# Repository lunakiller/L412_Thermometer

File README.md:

# L412 Thermometer
Temperature and humidity station powered by STM32L412KB MCU. The goal of the project is the longest possible battery life.

## Main components
- STM32L412KBT6 MCU
- Si7021 temperature and humidity sensor
- LCD display with PCD8544 driver
- 600mAh Li-Ion battery

## Goals
- [x] Build it on the breadboard
- [x] Show temperature and humidity data on the display
- [x] Run from the battery
- [x] Design PCB
- [ ] Measure battery voltage
- [ ] Sync time through USB
- [ ] Design 3D printed case

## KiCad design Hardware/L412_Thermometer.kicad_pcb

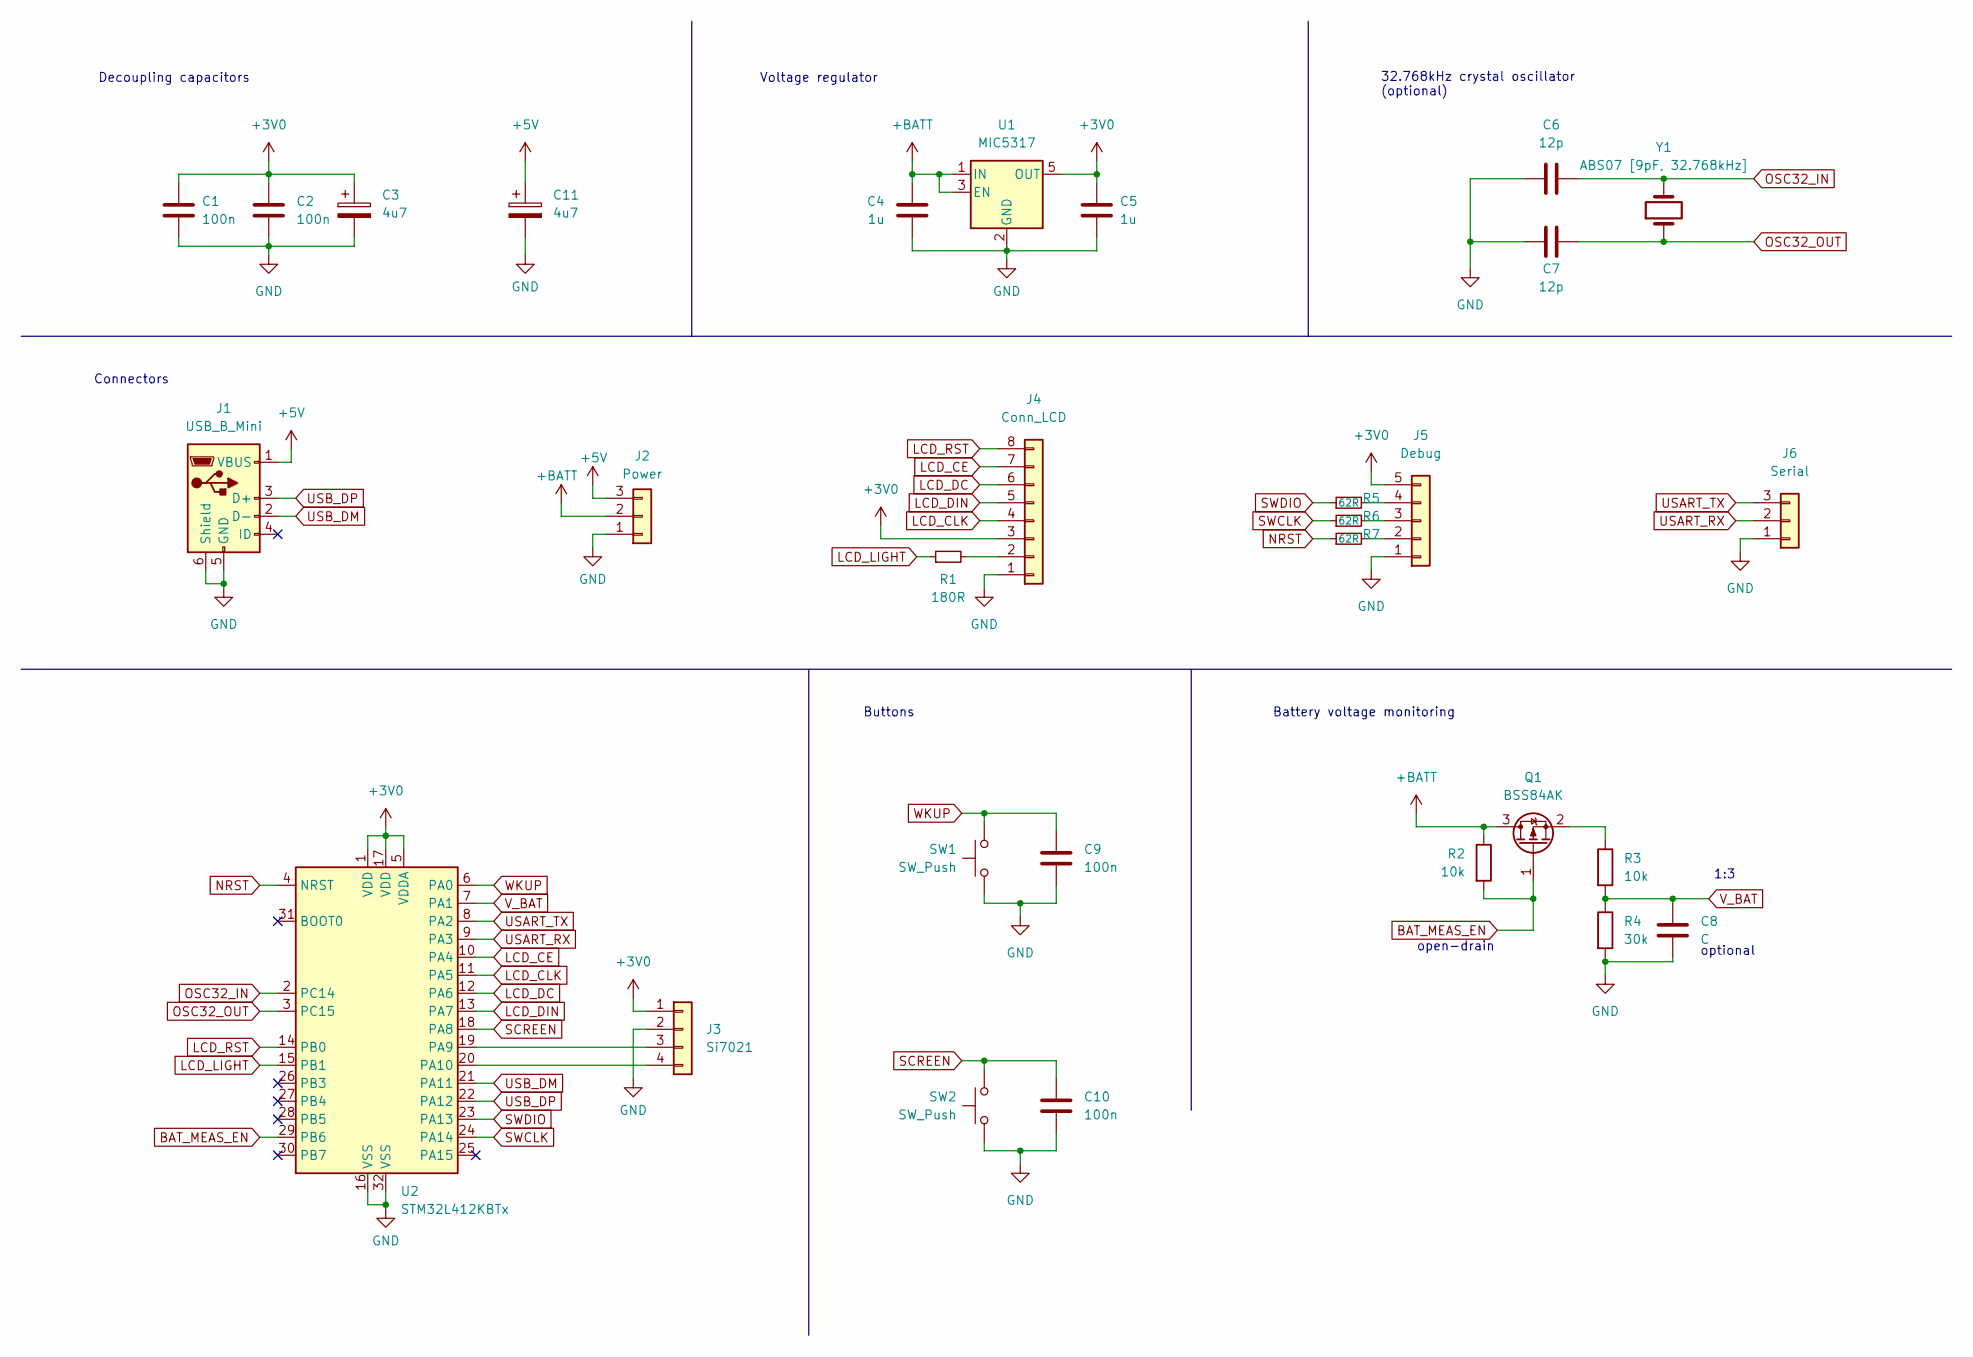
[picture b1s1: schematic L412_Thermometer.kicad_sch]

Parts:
C1, C2, C9, C10: 100n; C_0603_1608Metric
C3, C11: 4u7; CP_EIA-1608-10_AVX-L
C4, C5: 1u; C_0603_1608Metric
C6, C7: 12p; C_0603_1608Metric
C8: C; C_0603_1608Metric
J1: USB_B_Mini; USB_Mini-B_Lumberg_2486_01_Horizontal
J2: Power; PinHeader_1x03_P2.54mm_Vertical
J3: Si7021; PinHeader_1x04_P2.54mm_Vertical
J4: Conn_LCD; PinHeader_1x08_P2.54mm_Vertical
J5: Debug; PinHeader_1x05_P2.54mm_Vertical
J6: Serial; PinHeader_1x03_P2.54mm_Vertical
Q1: BSS84AK; SOT-23
R1: 180R; R_0603_1608Metric
R2, R3: 10k; R_0603_1608Metric
R4: 30k; R_0603_1608Metric
R5, R6, R7: 62R; R_0603_1608Metric
SW1, SW2: SW_Push; SW_SPST_SKQG_WithStem
U1: MIC5317; SOT-23-5
U2: STM32L412KBTx; LQFP-32_7x7mm_P0.8mm
Y1: ABS07 [9pF, 32.768kHz]; Crystal_SMD_3215-2Pin_3.2x1.5mm

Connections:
+3V0: C1.1, C2.1, C3.1, C5.1, J3.1, J4.3, J5.5, U1.5 (OUT), U2.1 (VDD), U2.5 (VDDA), U2.17 (VDD)
+5V: C11.1, J1.1 (VBUS), J2.3
+BATT: C4.1, J2.2, Q1.3 (D), R2.1, U1.1 (IN), U1.3 (EN)
BAT_MEAS_EN: Q1.1 (G), R2.2, U2.29 (PB6)
GND: C1.2, C2.2, C3.2, C4.2, C5.2, C6.1, C7.1, C8.2, C9.2, C10.2, C11.2, J1.5 (GND), J1.6 (Shield), J2.1, J3.2, J4.1, J5.1, J6.1, R4.2, SW1.1, SW2.1, U1.2 (GND), U2.16 (VSS), U2.32 (VSS)
LCD_CE: J4.7, U2.10 (PA4)
LCD_CLK: J4.4, U2.11 (PA5)
LCD_DC: J4.6, U2.12 (PA6)
LCD_DIN: J4.5, U2.13 (PA7)
LCD_LIGHT: R1.1, U2.15 (PB1)
LCD_RST: J4.8, U2.14 (PB0)
NRST: R7.1, U2.4 (NRST)
unnamed: J3.3, U2.19 (PA9)
unnamed: J3.4, U2.20 (PA10)
unnamed: J4.2, R1.2
unnamed: J5.2, R7.2
unnamed: J5.3, R6.2
unnamed: J5.4, R5.2
unnamed: Q1.2 (S), R3.1
OSC32_IN: C6.2, U2.2 (PC14), Y1.2
OSC32_OUT: C7.2, U2.3 (PC15), Y1.1
SCREEN: C10.1, SW2.2, U2.18 (PA8)
SWCLK: R6.1, U2.24 (PA14)
SWDIO: R5.1, U2.23 (PA13)
USART_RX: J6.2, U2.9 (PA3)
USART_TX: J6.3, U2.8 (PA2)
USB_DM: J1.2 (D-), U2.21 (PA11)
USB_DP: J1.3 (D+), U2.22 (PA12)
V_BAT: C8.1, R3.2, R4.1, U2.7 (PA1)
WKUP: C9.1, SW1.2, U2.6 (PA0)

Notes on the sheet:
1:3
Battery voltage monitoring
Buttons
open-drain
optional
32.768kHz crystal oscillator (optional)
Voltage regulator
Decoupling capacitors
Connectors

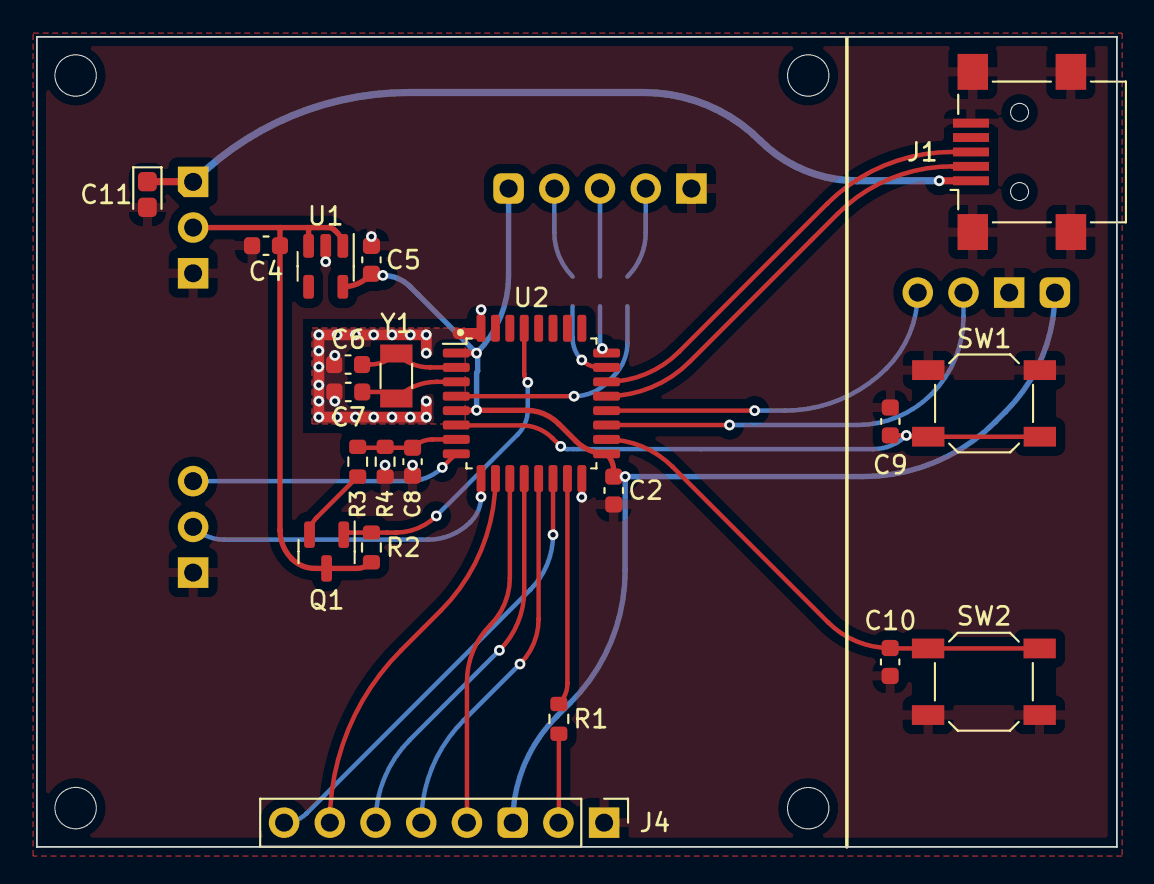
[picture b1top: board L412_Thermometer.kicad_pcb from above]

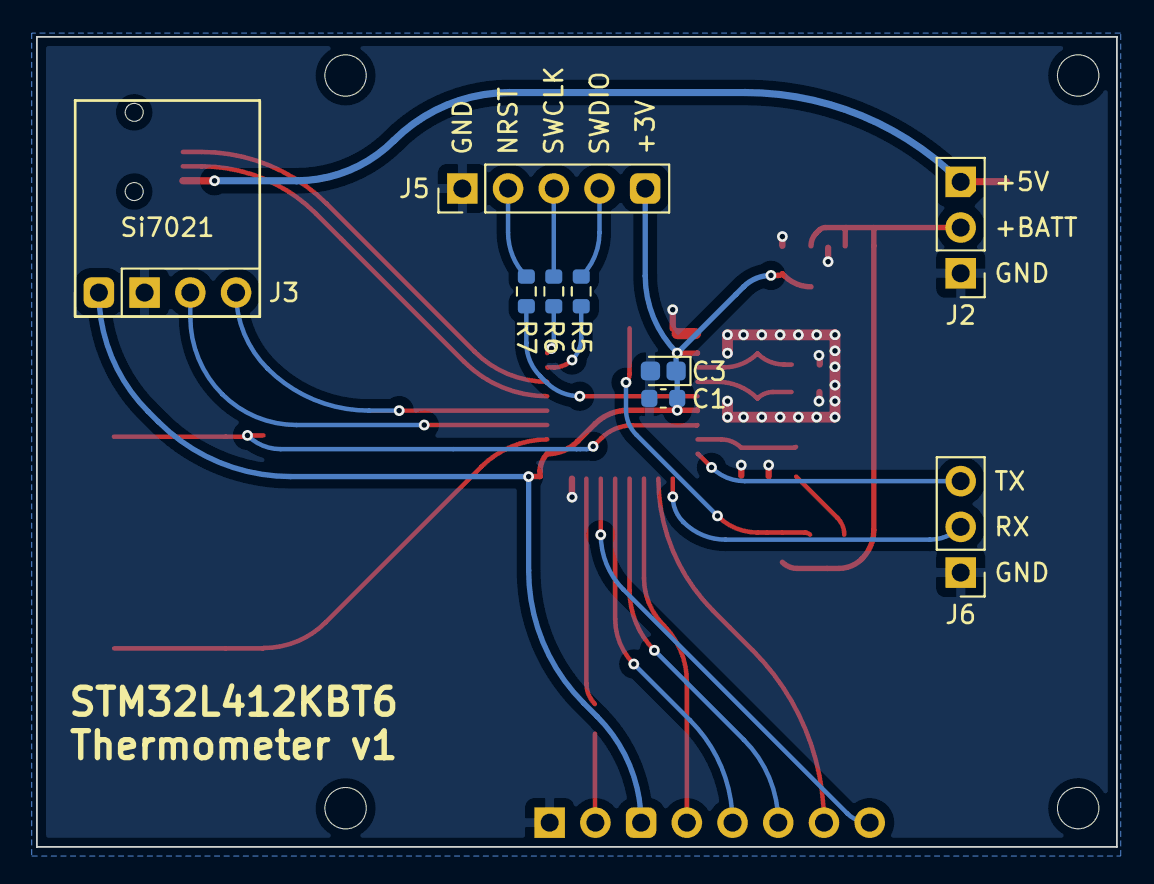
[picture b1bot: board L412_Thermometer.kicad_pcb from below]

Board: 2 copper layers, 60.0 x 45.0 mm, 30 parts (9 on the bottom side), 30 nets.

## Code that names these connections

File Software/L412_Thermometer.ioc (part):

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Mcu.Name=STM32L412KBTx
Mcu.Package=LQFP32
Mcu.UserName=STM32L412KBTx
PA0-CK_IN.GPIOParameters=GPIO_PuPd,GPIO_Label,GPIO_ModeDefaultEXTI
PA0-CK_IN.GPIO_Label=WKUP
PA0-CK_IN.GPIO_ModeDefaultEXTI=GPIO_MODE_IT_FALLING
PA0-CK_IN.GPIO_PuPd=GPIO_PULLUP
PA0-CK_IN.Signal=GPXTI0
PA1.GPIOParameters=GPIO_Label
PA1.GPIO_Label=V_BAT
PA1.Signal=ADCx_IN6
PA10.GPIOParameters=GPIO_Label,GPIO_Pu
PA10.GPIO_Label=SI7021_SDA
PA10.GPIO_Pu=GPIO_PULLUP
PA10.Mode=I2C
PA10.Signal=I2C1_SDA
PA11.Mode=Device
PA11.Signal=USB_DM
PA12.Mode=Device
PA12.Signal=USB_DP
PA13\ (JTMS/SWDIO).Mode=Serial_Wire
PA13\ (JTMS/SWDIO).Signal=SYS_JTMS-SWDIO
PA14\ (JTCK/SWCLK).Mode=Serial_Wire
PA14\ (JTCK/SWCLK).Signal=SYS_JTCK-SWCLK
PA2.Mode=Asynchronous
PA2.Signal=LPUART1_TX
PA3.Mode=Asynchronous
PA3.Signal=LPUART1_RX
PA4.GPIOParameters=GPIO_Label
PA4.GPIO_Label=LCD_CE
PA4.Signal=GPIO_Output
PA5.GPIOParameters=GPIO_Label
PA5.GPIO_Label=LCD_CLK
PA5.Mode=TX_Only_Simplex_Unidirect_Master
PA5.Signal=SPI1_SCK
PA6.GPIOParameters=GPIO_Label
PA6.GPIO_Label=LCD_DC
PA6.Signal=GPIO_Output
PA7.GPIOParameters=GPIO_Label
PA7.GPIO_Label=LCD_DIN
PA7.Mode=TX_Only_Simplex_Unidirect_Master
PA7.Signal=SPI1_MOSI
PA8.GPIOParameters=GPIO_PuPd,GPIO_Label,GPIO_ModeDefaultEXTI
PA8.GPIO_Label=SCREEN
PA8.GPIO_ModeDefaultEXTI=GPIO_MODE_IT_FALLING
PA8.GPIO_PuPd=GPIO_PULLUP
PA8.Signal=GPXTI8
PA9.GPIOParameters=GPIO_Label,GPIO_Pu
PA9.GPIO_Label=SI7021_CSL
PA9.GPIO_Pu=GPIO_PULLUP
PA9.Mode=I2C
PA9.Signal=I2C1_SCL
PB0.GPIOParameters=GPIO_Label
PB0.GPIO_Label=LCD_RST
PB0.Signal=GPIO_Output
PB1.GPIOParameters=PinState,GPIO_PuPd,GPIO_Label,GPIO_ModeDefaultOutputPP
PB1.GPIO_Label=LCD_LIGHT
PB1.GPIO_ModeDefaultOutputPP=GPIO_MODE_OUTPUT_OD
PB1.GPIO_PuPd=GPIO_PULLUP
PB1.PinState=GPIO_PIN_SET
PB1.Signal=GPIO_Output
PB6.GPIOParameters=GPIO_Label
PB6.GPIO_Label=BAT_MEAS_EN
PB6.Signal=GPIO_Output
RCC.HSE_VALUE=8000000
RCC.SYSCLKFreq_VALUE=48000000
board=custom

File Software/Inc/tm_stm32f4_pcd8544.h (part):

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 *
 *  LCD BOARD   STM32F444   DESCRIPTION
 *
 *  RST         PC15        Reset pin for LCD
 *  CE          PC13        Chip enable for SPI2
 *  DC          PC14        Data/Command pin
 *  DIN         PC3         MOSI pin for SPI2
 *  CLK         PB10        CLOCK pin for SPI2
 *  VCC         3.3V        VCC Power
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//Default RST pin
#ifndef PCD8544_RST_PIN
#define PCD8544_RST_RCC         RCC_AHB1Periph_GPIOB
#define PCD8544_RST_PORT        LCD_RST_GPIO_Port
#define PCD8544_RST_PIN         LCD_RST_Pin
#endif
//Default DC pin
#ifndef PCD8544_DC_PIN
#define PCD8544_DC_RCC          RCC_AHB1Periph_GPIOA
#define PCD8544_DC_PORT         LCD_DC_GPIO_Port
#define PCD8544_DC_PIN          LCD_DC_Pin
#endif
//Default CE pin
#ifndef PCD8544_CE_PIN
#define PCD8544_CE_RCC          RCC_AHB1Periph_GPIOA
#define PCD8544_CE_PORT         LCD_CE_GPIO_Port
#define PCD8544_CE_PIN          LCD_CE_Pin
#endif

#define PCD8544_CE_LOW          HAL_GPIO_WritePin(PCD8544_CE_PORT, PCD8544_CE_PIN, GPIO_PIN_RESET)
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
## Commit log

2022-07-26 Upload files
2022-07-27 formatting changes
2022-08-09 Version for breadboard testing
2022-08-09 PCB updated
2022-08-09 Migration to newer CubeMX and firmware
2022-08-17 Changed SW2 pin assignment
2022-08-17 Routed PCB
2022-08-18 Voltage divider values, changed footprint of P-MOS, picked a voltage regulator

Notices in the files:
Software/Inc/tm_stm32f4_pcd8544.h:
@license GNU GPL v3
| Copyright (C) Tilen MAJERLE, 2014
| it under the terms of the GNU General Public License as published by
| the Free Software Foundation, either version 3 of the License, or
| any later version.
